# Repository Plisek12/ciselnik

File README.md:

# ciselnik
Tišťák číselník, který umí zobrazovat nastavene elementy. Vyrobeno pro firmu La Lorraine. Navržen tak, aby se zabránilo chybovosti obsluhy při obsluze stroje od společnosti Mecatherm.

Toto je test

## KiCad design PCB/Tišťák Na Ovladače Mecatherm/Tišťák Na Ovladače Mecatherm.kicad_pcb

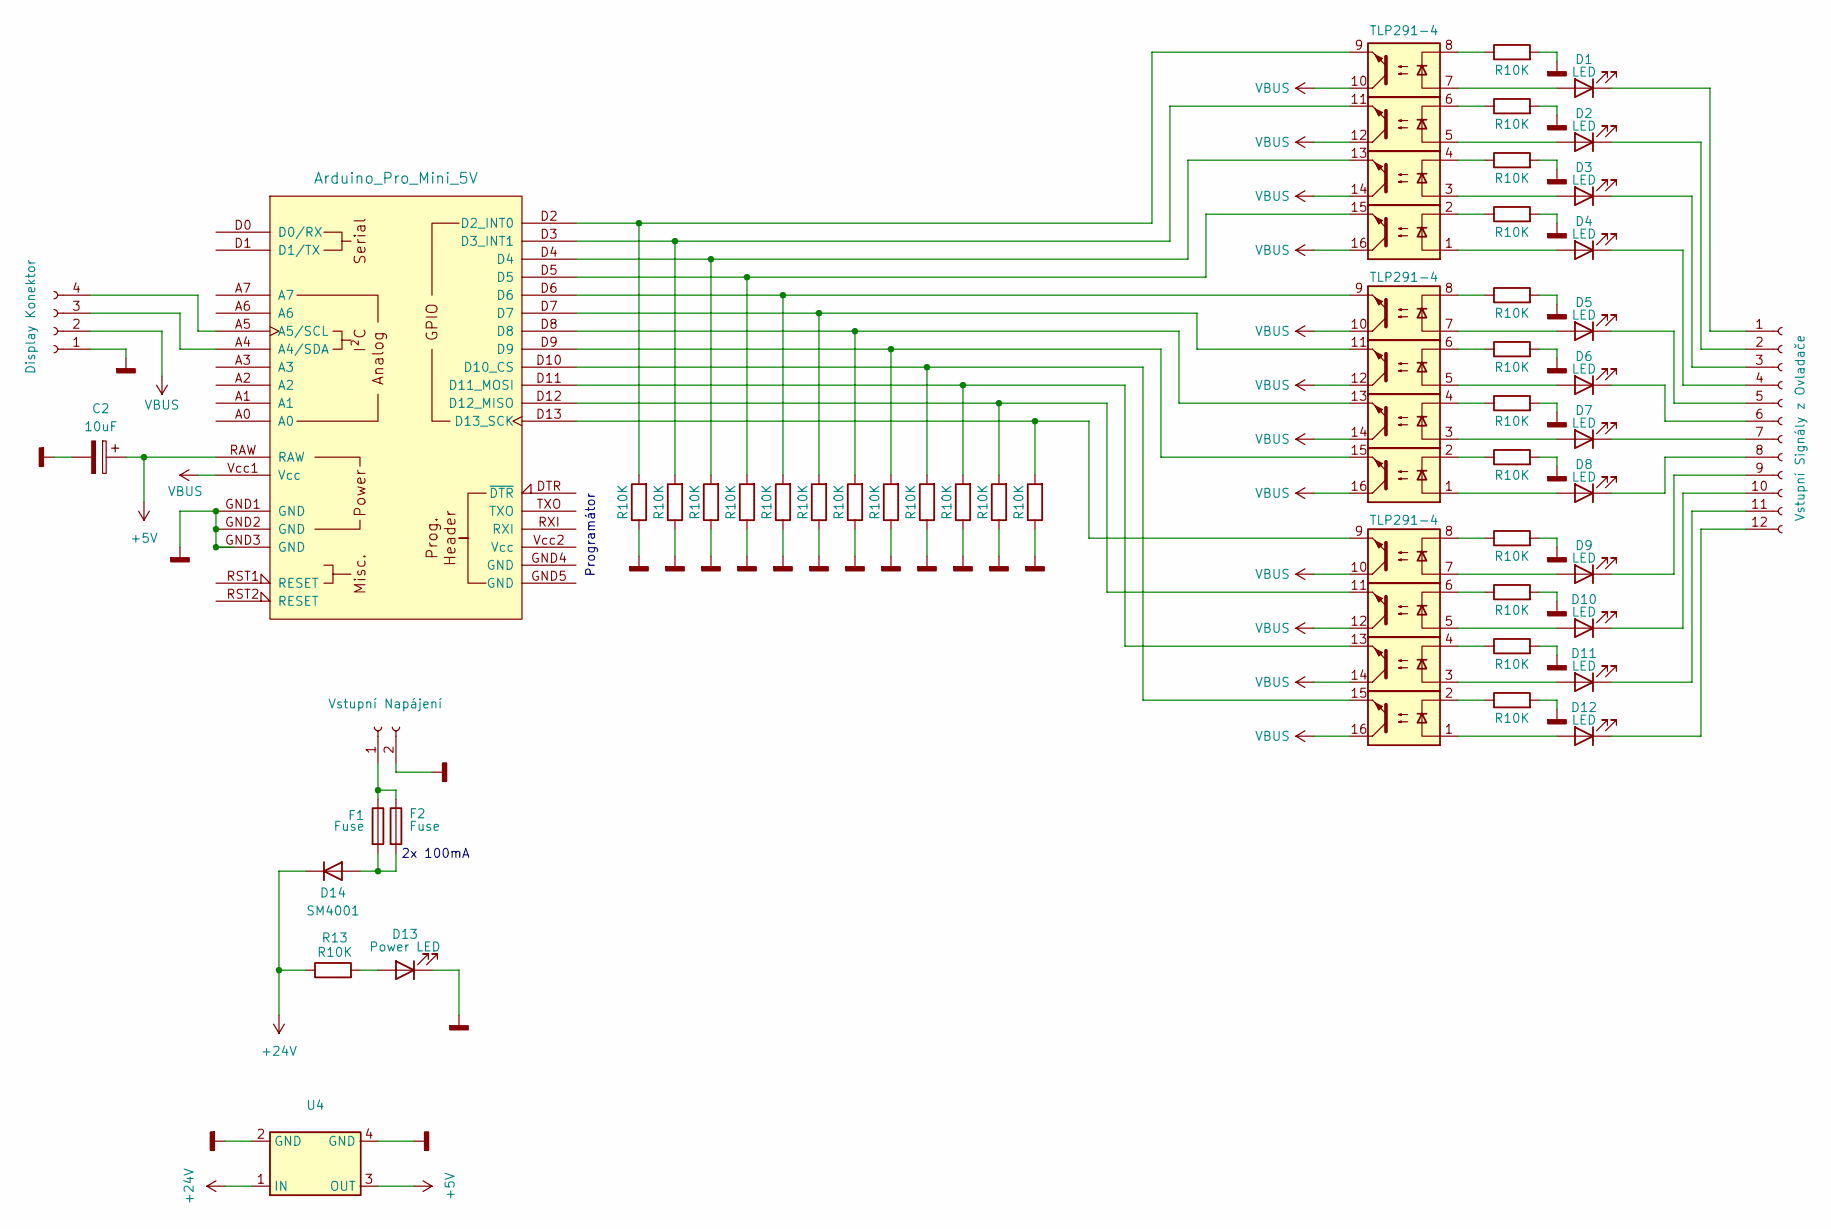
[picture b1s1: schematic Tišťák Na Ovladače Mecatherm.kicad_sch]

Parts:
A2: Arduino_Pro_Mini_5V; Clone_Pro_Mini_Socket_NoSPH
C2: 10uF; CP_Radial_D5.0mm_P2.50mm
D1, D2, D3, D4, D5, D6, D7, D8, D9, D10, D11, D12: LED; LED_0805_2012Metric
D13: Power LED; LED_0805_2012Metric
D14: SM4001; D_MELF
F1, F2: Fuse; Fuse_1206_3216Metric
J1: Vstupní Signály z Ovladače; PinHeader_1x12_P2.54mm_Vertical
J2: Vstupní Napájení; PinHeader_1x02_P2.00mm_Vertical
J3: Display Konektor; PinHeader_1x04_P1.00mm_Vertical
R1, R2, R3, R4, R5, R6, R7, R8, R9, R10, R11, R12: R10K; R_1206_3216Metric
R13, R14, R15, R16, R17, R18, R19, R20, R21, R22, R23, R24, R25: R10K; R_0805_2012Metric
U1, U2, U3: TLP291-4; SOIC-16_4.55x10.3mm_P1.27mm
U4: StepDown_Module

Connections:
+5V: A2.RAW, C2.1, U4.3 (OUT)
+24V: D14.1 (K), R13.1, U4.1 (IN)
GNDD: A2.GND1 (GND), A2.GND2 (GND), A2.GND3 (GND), C2.2, D13.1 (K), J2.2, J3.1, R1.2, R2.2, R3.2, R4.2, R5.2, R6.2, R7.2, R8.2, R9.2, R10.2, R11.2, R12.2, R14.1, R15.1, R16.1, R17.1, R18.1, R19.1, R20.1, R21.1, R22.1, R23.1, R24.1, R25.1, U4.2 (GND), U4.4 (GND)
unnamed: A2.A4 (A4/SDA), J3.3
unnamed: A2.A5 (A5/SCL), J3.4
unnamed: A2.D2 (D2_INT0), R14.2, U1.9
unnamed: A2.D3 (D3_INT1), R15.2, U1.11
unnamed: A2.D10 (D10_CS), R22.2, U3.15
unnamed: A2.D11 (D11_MOSI), R23.2, U3.13
unnamed: A2.D12 (D12_MISO), R24.2, U3.11
unnamed: A2.D13 (D13_SCK), R25.2, U3.9
unnamed: A2.D4, R16.2, U1.13
unnamed: A2.D5, R17.2, U1.15
unnamed: A2.D6, R18.2, U2.9
unnamed: A2.D7, R19.2, U2.11
unnamed: A2.D8, R20.2, U2.13
unnamed: A2.D9, R21.2, U2.15
unnamed: D1.2 (A), U1.7
unnamed: D1.1 (K), J1.1
unnamed: D2.2 (A), U1.5
unnamed: D2.1 (K), J1.2
unnamed: D3.2 (A), U1.3
unnamed: D3.1 (K), J1.3
unnamed: D4.2 (A), U1.1
unnamed: D4.1 (K), J1.4
unnamed: D5.2 (A), U2.7
unnamed: D5.1 (K), J1.5
unnamed: D6.2 (A), U2.5
unnamed: D6.1 (K), J1.6
unnamed: D7.2 (A), U2.3
unnamed: D7.1 (K), J1.7
unnamed: D8.2 (A), U2.1
unnamed: D8.1 (K), J1.8
unnamed: D9.2 (A), U3.7
unnamed: D9.1 (K), J1.9
unnamed: D10.2 (A), U3.5
unnamed: D10.1 (K), J1.10
unnamed: D11.2 (A), U3.3
unnamed: D11.1 (K), J1.11
unnamed: D12.2 (A), U3.1
unnamed: D12.1 (K), J1.12
unnamed: D13.2 (A), R13.2
unnamed: D14.2 (A), F1.2, F2.2
unnamed: F1.1, F2.1, J2.1
unnamed: R1.1, U1.8
unnamed: R2.1, U1.6
unnamed: R3.1, U1.4
unnamed: R4.1, U1.2
unnamed: R5.1, U2.8
unnamed: R6.1, U2.6
unnamed: R7.1, U2.4
unnamed: R8.1, U2.2
unnamed: R9.1, U3.8
unnamed: R10.1, U3.6
unnamed: R11.1, U3.4
unnamed: R12.1, U3.2
VBUS: A2.Vcc1 (Vcc), J3.2, U1.10, U1.12, U1.14, U1.16, U2.10, U2.12, U2.14, U2.16, U3.10, U3.12, U3.14, U3.16

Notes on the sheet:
Programátor
2x 100mA

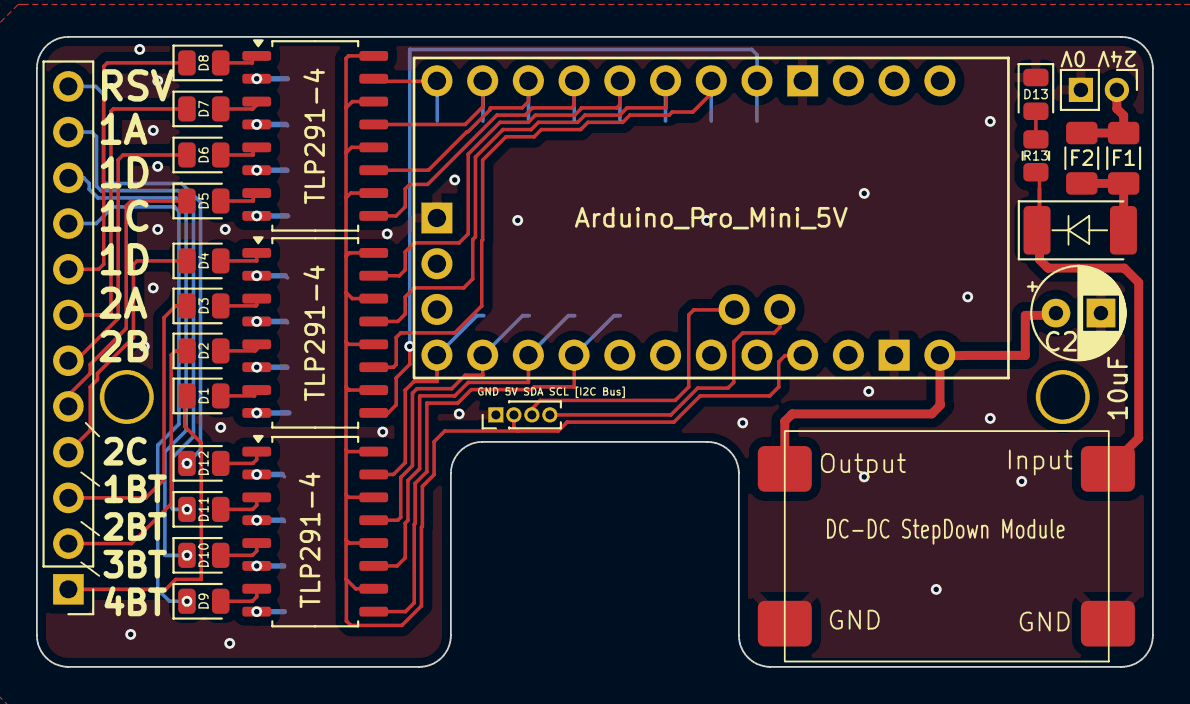
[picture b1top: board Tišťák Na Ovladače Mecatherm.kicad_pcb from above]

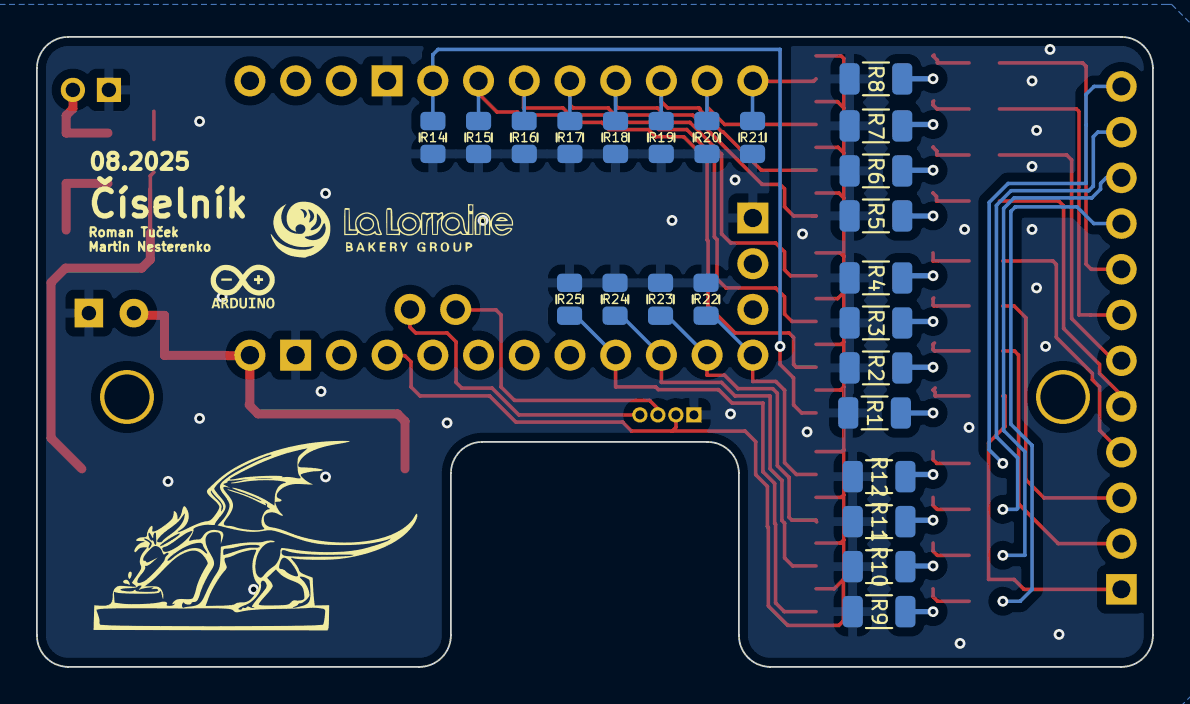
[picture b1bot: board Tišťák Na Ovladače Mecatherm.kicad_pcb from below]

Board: 2 copper layers, 62.0 x 35.0 mm, 50 parts (24 on the bottom side), 57 nets.

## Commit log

2025-08-15 Technologický Zobrazovač
    Tišťák s alfanumerickým displayem, pro ovladače společnosti Mecatherm
2025-08-15 aa
    aa
